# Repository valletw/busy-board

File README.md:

# Busy Board

My son wanted a busy board and I took the challenge to do my own, fully managed
by hardware (no MCU, no software).

Here is a fully hardware managed busy board with buttons & LEDs and an incremental
counter displayed on 7-segments display or LEDs track. Counter increment speed
can be switched with rotary switch from manual (button) to 4 Hz. To avoid buying
coin cells, I added a Lithium battery charger with an USB-C port: charge power
can be set with a DIP switch.

## Hardware

Power:

- USB-C Lipo battery charger (check EEMB 3.7V battery)
- Power switch to completely cut the power supply
- Polarity check
- LED are powered with 3.3V (LDO) or 5V (Boost regulator) from battery

Frequencies (improve battery consumption):

- An RC oscillator generate a 512 Hz frequency
- A binary counter generate multiple sub-frequencies from the 512 Hz
- A saw signal is generate from 128 Hz to generate LED PWM
- PWM duty cycle can be adjusted with potentiometer

Switches:

- 6 push switches that control 6 LEDs: Red, Orange, Green, White, Blue and Purple
- 3 rotary switch to control Red, Green, Blue LED power (change PWM duty cycle)
- Counter selector to switch between: 7-segments, LED track or unique LED
- Rotary switch to select counter speed: Button, 0.5 Hz, 1 Hz, 2 Hz or 4 Hz.

Note: All switches are similar but mechanical part will be 3D printed to provide
multiple type of switches: Push, Rocker, Toggle, Rotary, Key, Wire.

### Manufacturing

The board is manufactured by [JLCPCB](https://jlcpcb.com), here is the details
you will require to generate an order.

*Note: JLCPCB requests some modifications on output files, do not use direct
export from KiCad (check the FAQ)*

#### PCB

Files: [Gerbers](jlcpcb/gerbers.zip)

Configuration              | Value
---------------------------|---------------------------------
Base Materiel              | FR-4
Layers                     | 4
Dimensions                 | 140 x 180 mm
Different design           | 1
Delivery format            | Single PCB
PCB thickness              | 1.0 mm
PCB color                  | Green (other colors have fees)
Silkscreen                 | White
Materiel type              | FR4 TG135
Surface finish             | LeadFree HASL
Specify stackup            | No requirement
Via covering               | Plugged
Min via hole size/diameter | 0.3mm/0.45mm

*Note: All options have not been detail here, keep default value.*

#### Assembly

The project use 54 references with 26 extended. Extended parts bring extra cost
during assembly, around ~3$ per reference (no matter the number of components to
solder). To reduce the cost for small batch I propose two assembly configuration:

- Full: All managed by JLCPCB
- Partial: Basic parts and few extended parts are assembled per JLCPCB, and
  remaining parts can be buy on LCSC and soldered manually.

Files:

- [BOM Full](jlcpcb/bom-full.csv)
- [BOM Partial](jlcpcb/bom-partial.csv) - [BOM Extended](jlcpcb/bom-extended.csv)
- [CPL](jlcpcb/cpl.csv)

Configuration           | Value
------------------------|--------------------
PCBA type               | Economic
Assembly side           | Top
Tooling holes           | Added by JLCPCB
Confirm Parts Placement | Yes

Verify "pick & place" orientations and positions on the web viewer

*Note: All options have not been detail here, keep default value.*

## Mechanical

3D printed parts will be provided in this repository: casing, switches, light guides.

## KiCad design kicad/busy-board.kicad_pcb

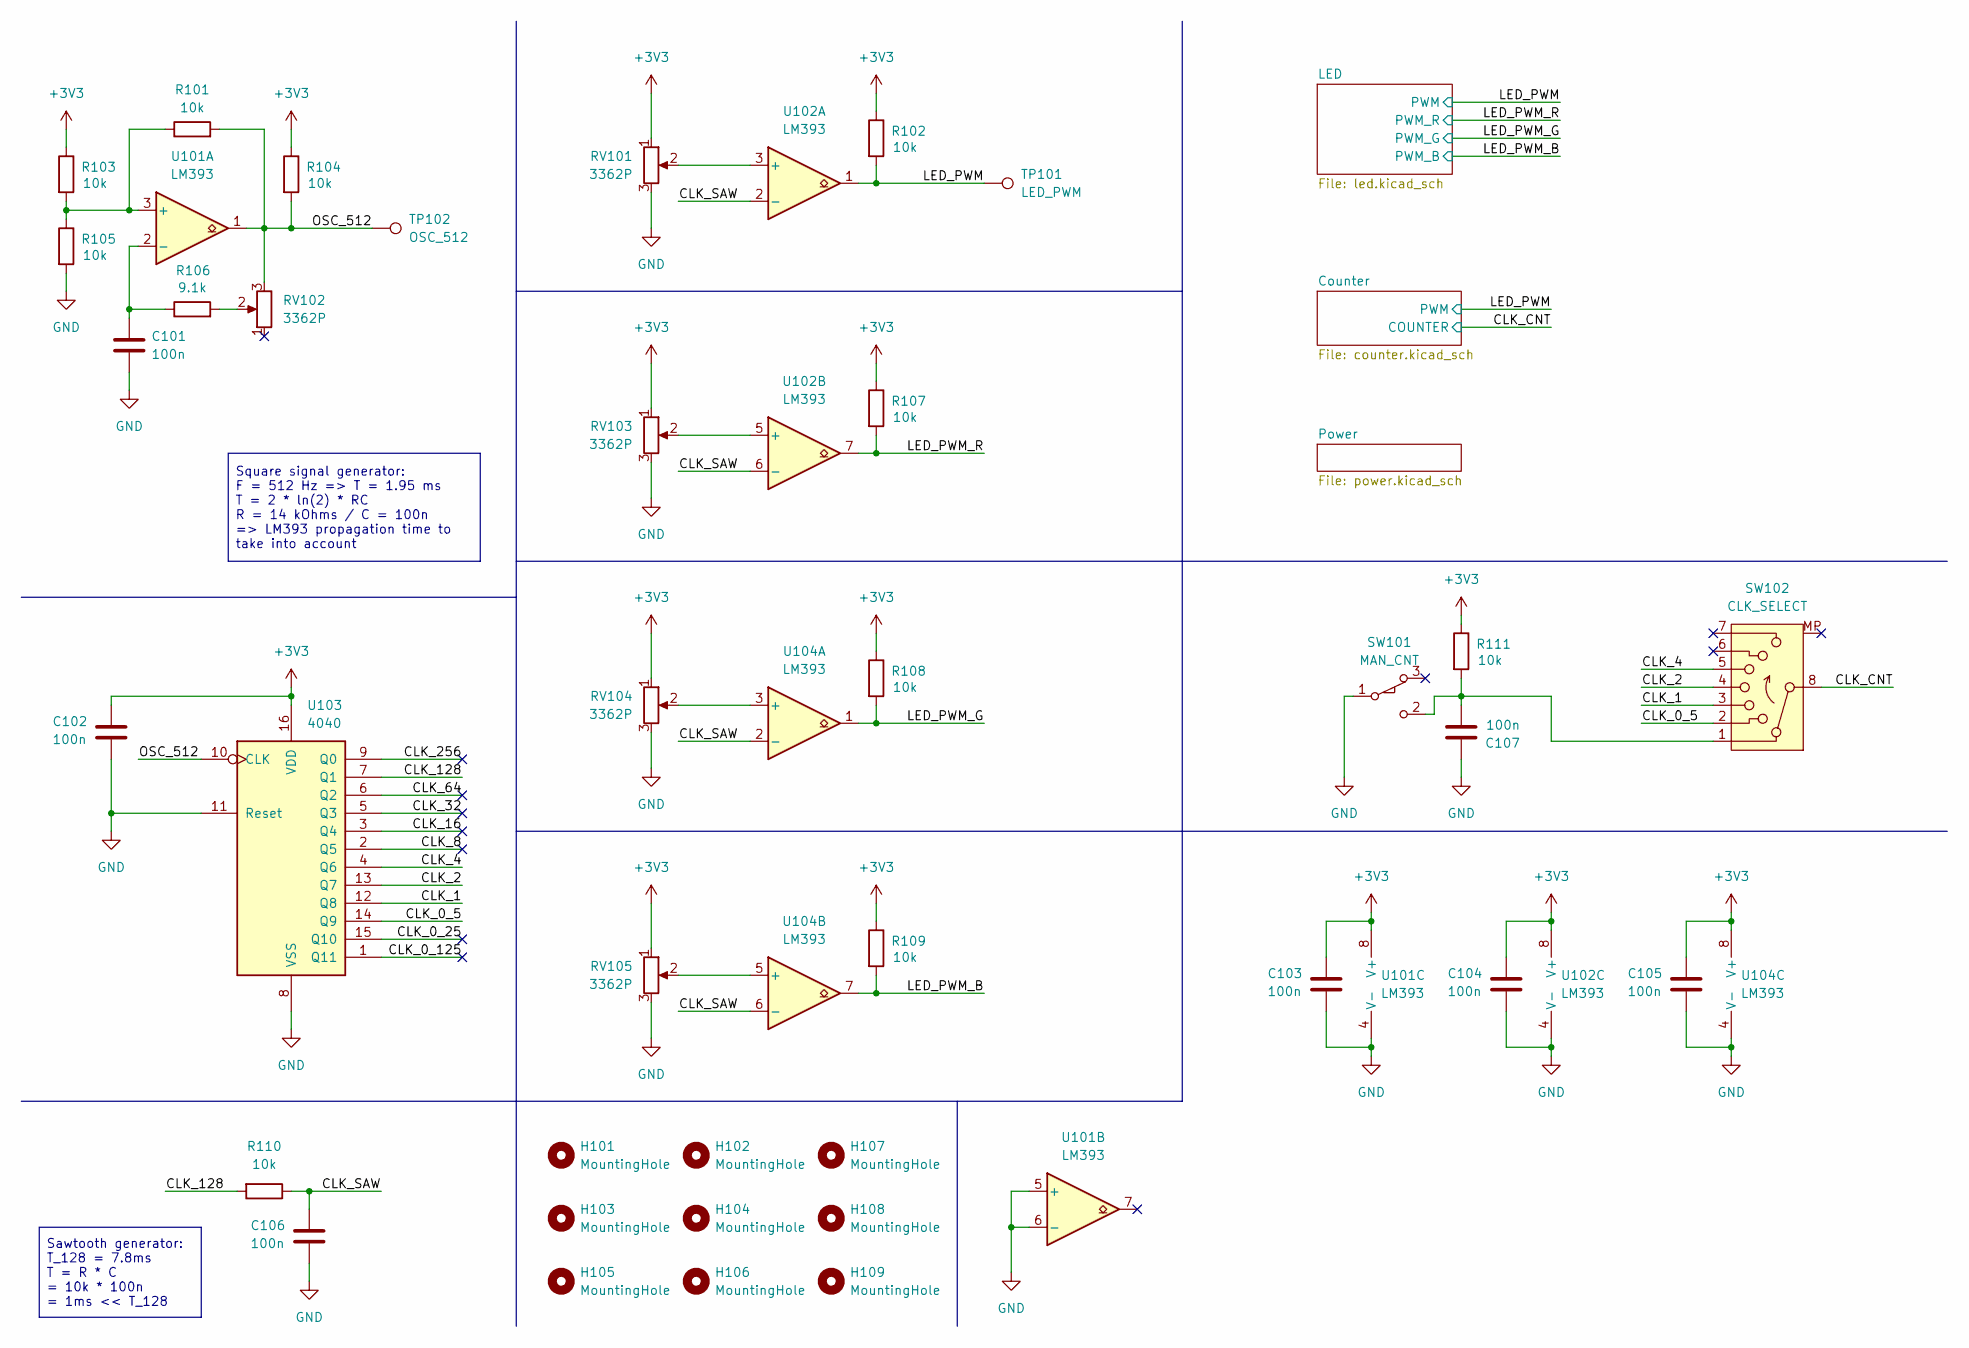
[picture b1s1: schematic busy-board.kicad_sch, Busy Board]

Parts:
C101: 100n; C_0603_1608Metric; MFR Part # CC0603JRX7R7BB104; LCSC Part # C91183
C102, C103, C104, C105, C106, C107: 100n; C_0402_1005Metric; MFR Part # CL05B104KB54PNC; LCSC Part # C307331
H101, H102, H103, H104, H105, H106, H107, H108, H109: MountingHole; MountingHole_2.7mm_M2.5_ISO7380
R101, R102, R103, R104, R105, R107, R108, R109, R110, R111: 10k; R_0603_1608Metric; MFR Part # 0603WAF1002T5E; LCSC Part # C25804
R106: 9.1k; R_0603_1608Metric; MFR Part # 0603WAF9101T5E; LCSC Part # C23260
RV101, RV102, RV103, RV104, RV105: 3362P; BOURNS_3362P; MFR Part # 3362P-1-103LF; LCSC Part # C58159
SW101: MAN_CNT; SW-TH_DM1-12UP-1; MFR Part # DM1-12UP-1; LCSC Part # C405949
SW102: CLK_SELECT; SW-TH_RT-0C4-D; MFR Part # RT-0C5; LCSC Part # C508440
TP101: LED_PWM; TestPoint_Pad_D1.5mm
TP102: OSC_512; TestPoint_Pad_D1.5mm
U101, U102, U104: LM393; SOIC-8_3.9x4.9mm_P1.27mm; MFR Part # LM393DR2G; LCSC Part # C7955
U103: 4040; SOP-16_4.4x10.4mm_P1.27mm; MFR Part # CD4040BM/TR; LCSC Part # C725347

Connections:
+3V3: C102.1, C103.1, C104.1, C105.1, R102.1, R103.1, R104.1, R107.1, R108.1, R109.1, R111.1, RV101.1, RV103.1, RV104.1, RV105.1, U101.8 (V+), U102.8 (V+), U103.16 (VDD), U104.8 (V+); also elsewhere on the board
/CLK_0_5: SW102.2, U103.14 (Q9)
/CLK_0_25: U103.15 (Q10)
/CLK_0_125: U103.1 (Q11)
/CLK_1: SW102.3, U103.12 (Q8)
/CLK_2: SW102.4, U103.13 (Q7)
/CLK_4: SW102.5, U103.4 (Q6)
/CLK_8: U103.2 (Q5)
/CLK_16: U103.3 (Q4)
/CLK_32: U103.5 (Q3)
/CLK_64: U103.6 (Q2)
/CLK_128: R110.2, U103.7 (Q1)
/CLK_256: U103.9 (Q0)
/CLK_CNT: SW102.8; also elsewhere on the board
/CLK_SAW: C106.1, R110.1, U102.2 (-), U102.6 (-), U104.2 (-), U104.6 (-)
/LED_PWM: R102.2, TP101.1, U102.1; also elsewhere on the board
/LED_PWM_B: R109.2, U104.7; also elsewhere on the board
/LED_PWM_G: R108.2, U104.1; also elsewhere on the board
/LED_PWM_R: R107.2, U102.7; also elsewhere on the board
/OSC_512: R101.2, R104.2, RV102.3, TP102.1, U101.1, U103.10 (CLK)
GND: C101.2, C102.2, C103.2, C104.2, C105.2, C106.2, C107.1, R105.2, RV101.3, RV103.3, RV104.3, RV105.3, SW101.1 (A), U101.4 (V-), U101.5 (+), U101.6 (-), U102.4 (V-), U103.8 (VSS), U103.11 (Reset), U104.4 (V-); also elsewhere on the board
unnamed: R106.2, RV102.2
unnamed: C107.2, R111.2, SW101.2 (B), SW102.1
unnamed: R101.1, R103.2, R105.1, U101.3 (+)
unnamed: C101.1, R106.1, U101.2 (-)
unnamed: RV101.2, U102.3 (+)
unnamed: RV103.2, U102.5 (+)
unnamed: RV104.2, U104.3 (+)
unnamed: RV105.2, U104.5 (+)

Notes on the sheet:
Sawtooth generator: T_128 = 7.8ms T = R * C = 10k * 100n = 1ms << T_128
Square signal generator: F = 512 Hz => T = 1.95 ms T = 2 * ln(2) * RC R = 14 kOhms / C = 100n => LM393 propagation time to take into account

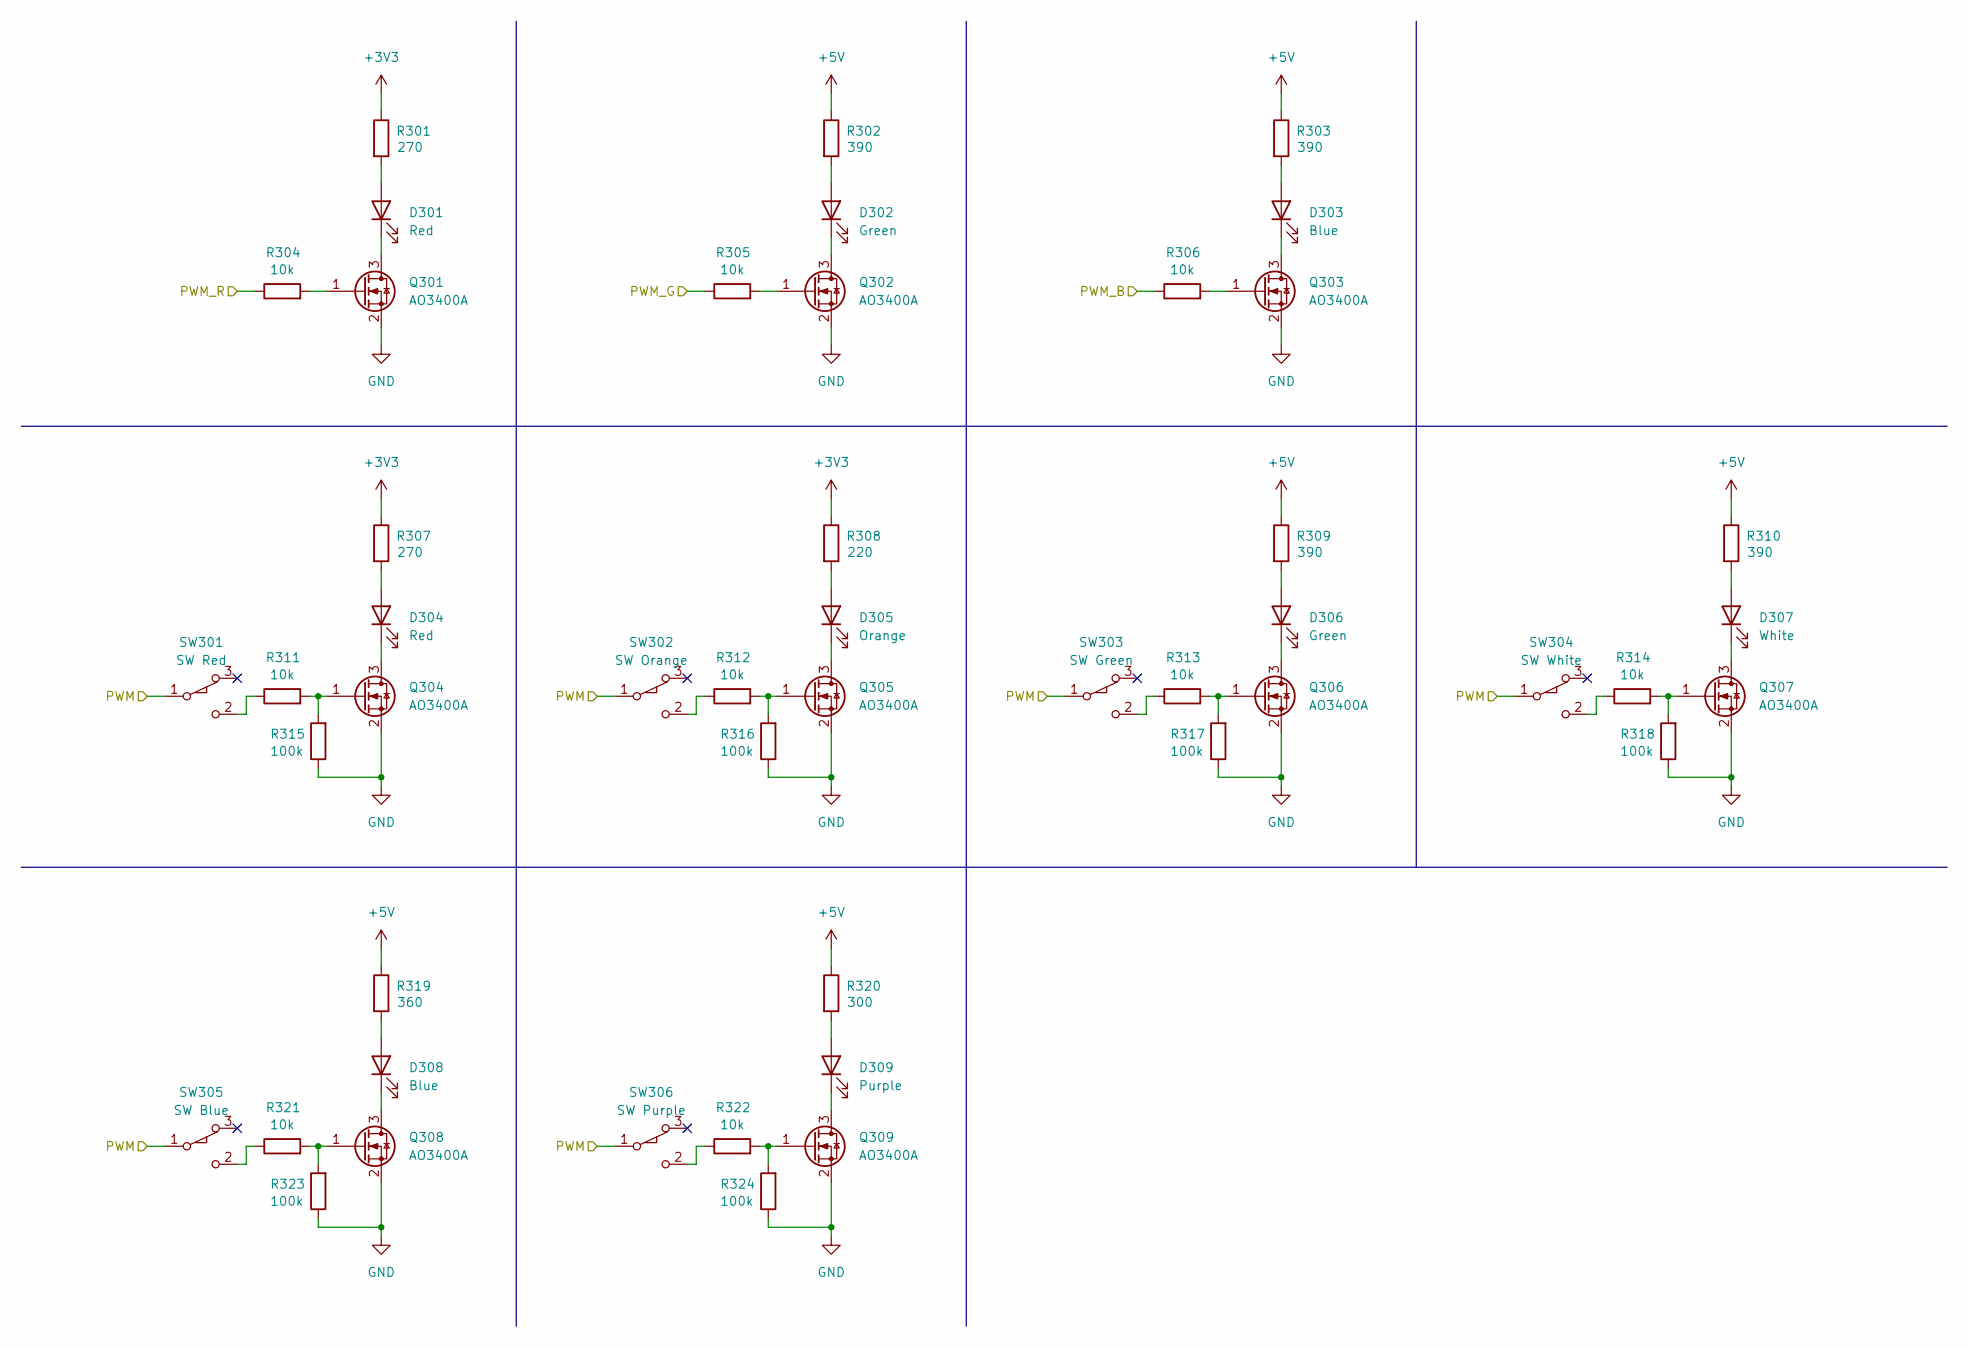
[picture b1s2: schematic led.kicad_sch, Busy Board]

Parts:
D301, D304: Red; LED_0805_2012Metric; MFR Part # NCD0805R1; LCSC Part # C84256
D302, D306: Green; LED_0805_2012Metric; MFR Part # KT-0805G; LCSC Part # C2297
D303, D308: Blue; LED_0805_2012Metric; MFR Part # NCD0805B2; LCSC Part # C84259
D305: Orange; LED_0805_2012Metric; MFR Part # NCD0805O1; LCSC Part # C84262
D307: White; LED_0805_2012Metric; MFR Part # KT-0805W; LCSC Part # C34499
D309: Purple; LED_0805_2012Metric; MFR Part # XL-2012UVA; LCSC Part # C7371915
Q301, Q302, Q303, Q304, Q305, Q306, Q307, Q308, Q309: AO3400A; SOT-23; MFR Part # AO3400A; LCSC Part # C20917
R301, R307: 270; R_0603_1608Metric; MFR Part # 0603WAF2700T5E; LCSC Part # C22966
R302, R303, R309, R310: 390; R_0603_1608Metric; MFR Part # 0603WAF3900T5E; LCSC Part # C23151
R304, R305, R306, R311, R312, R313, R314, R321, R322: 10k; R_0603_1608Metric; MFR Part # 0603WAF1002T5E; LCSC Part # C25804
R308: 220; R_0603_1608Metric; MFR Part # 0603WAF2200T5E; LCSC Part # C22962
R315, R316, R317, R318, R323, R324: 100k; R_0603_1608Metric; MFR Part # 0603WAF1003T5E; LCSC Part # C25803
R319: 360; R_0603_1608Metric; MFR Part # 0603WAF3600T5E; LCSC Part # C25194
R320: 300; R_0603_1608Metric; MFR Part # 0603WAF3000T5E; LCSC Part # C23025
SW301: SW Red; SW-TH_DM1-12UP-1; MFR Part # DM1-12UP-1; LCSC Part # C405949
SW302: SW Orange; SW-TH_DM1-12UP-1; MFR Part # DM1-12UP-1; LCSC Part # C405949
SW303: SW Green; SW-TH_DM1-12UP-1; MFR Part # DM1-12UP-1; LCSC Part # C405949
SW304: SW White; SW-TH_DM1-12UP-1; MFR Part # DM1-12UP-1; LCSC Part # C405949
SW305: SW Blue; SW-TH_DM1-12UP-1; MFR Part # DM1-12UP-1; LCSC Part # C405949
SW306: SW Purple; SW-TH_DM1-12UP-1; MFR Part # DM1-12UP-1; LCSC Part # C405949

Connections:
+3V3: R301.1, R307.1, R308.1; also elsewhere on the board
+5V: R302.1, R303.1, R309.1, R310.1, R319.1, R320.1; also elsewhere on the board
/LED_PWM: SW301.1 (A), SW302.1 (A), SW303.1 (A), SW304.1 (A), SW305.1 (A), SW306.1 (A); also elsewhere on the board
/LED_PWM_B: R306.1; also elsewhere on the board
/LED_PWM_G: R305.1; also elsewhere on the board
/LED_PWM_R: R304.1; also elsewhere on the board
GND: Q301.2 (S), Q302.2 (S), Q303.2 (S), Q304.2 (S), Q305.2 (S), Q306.2 (S), Q307.2 (S), Q308.2 (S), Q309.2 (S), R315.1, R316.1, R317.1, R318.1, R323.1, R324.1; also elsewhere on the board
unnamed: D301.2 (A), R301.2
unnamed: D301.1 (K), Q301.3 (D)
unnamed: D302.2 (A), R302.2
unnamed: D302.1 (K), Q302.3 (D)
unnamed: D303.2 (A), R303.2
unnamed: D303.1 (K), Q303.3 (D)
unnamed: D304.2 (A), R307.2
unnamed: D304.1 (K), Q304.3 (D)
unnamed: D305.2 (A), R308.2
unnamed: D305.1 (K), Q305.3 (D)
unnamed: D306.2 (A), R309.2
unnamed: D306.1 (K), Q306.3 (D)
unnamed: D307.2 (A), R310.2
unnamed: D307.1 (K), Q307.3 (D)
unnamed: D308.2 (A), R319.2
unnamed: D308.1 (K), Q308.3 (D)
unnamed: D309.2 (A), R320.2
unnamed: D309.1 (K), Q309.3 (D)
unnamed: Q301.1 (G), R304.2
unnamed: Q302.1 (G), R305.2
unnamed: Q303.1 (G), R306.2
unnamed: Q304.1 (G), R311.2, R315.2
unnamed: Q305.1 (G), R312.2, R316.2
unnamed: Q306.1 (G), R313.2, R317.2
unnamed: Q307.1 (G), R314.2, R318.2
unnamed: Q308.1 (G), R321.2, R323.2
unnamed: Q309.1 (G), R322.2, R324.2
unnamed: R311.1, SW301.2 (B)
unnamed: R312.1, SW302.2 (B)
unnamed: R313.1, SW303.2 (B)
unnamed: R314.1, SW304.2 (B)
unnamed: R321.1, SW305.2 (B)
unnamed: R322.1, SW306.2 (B)

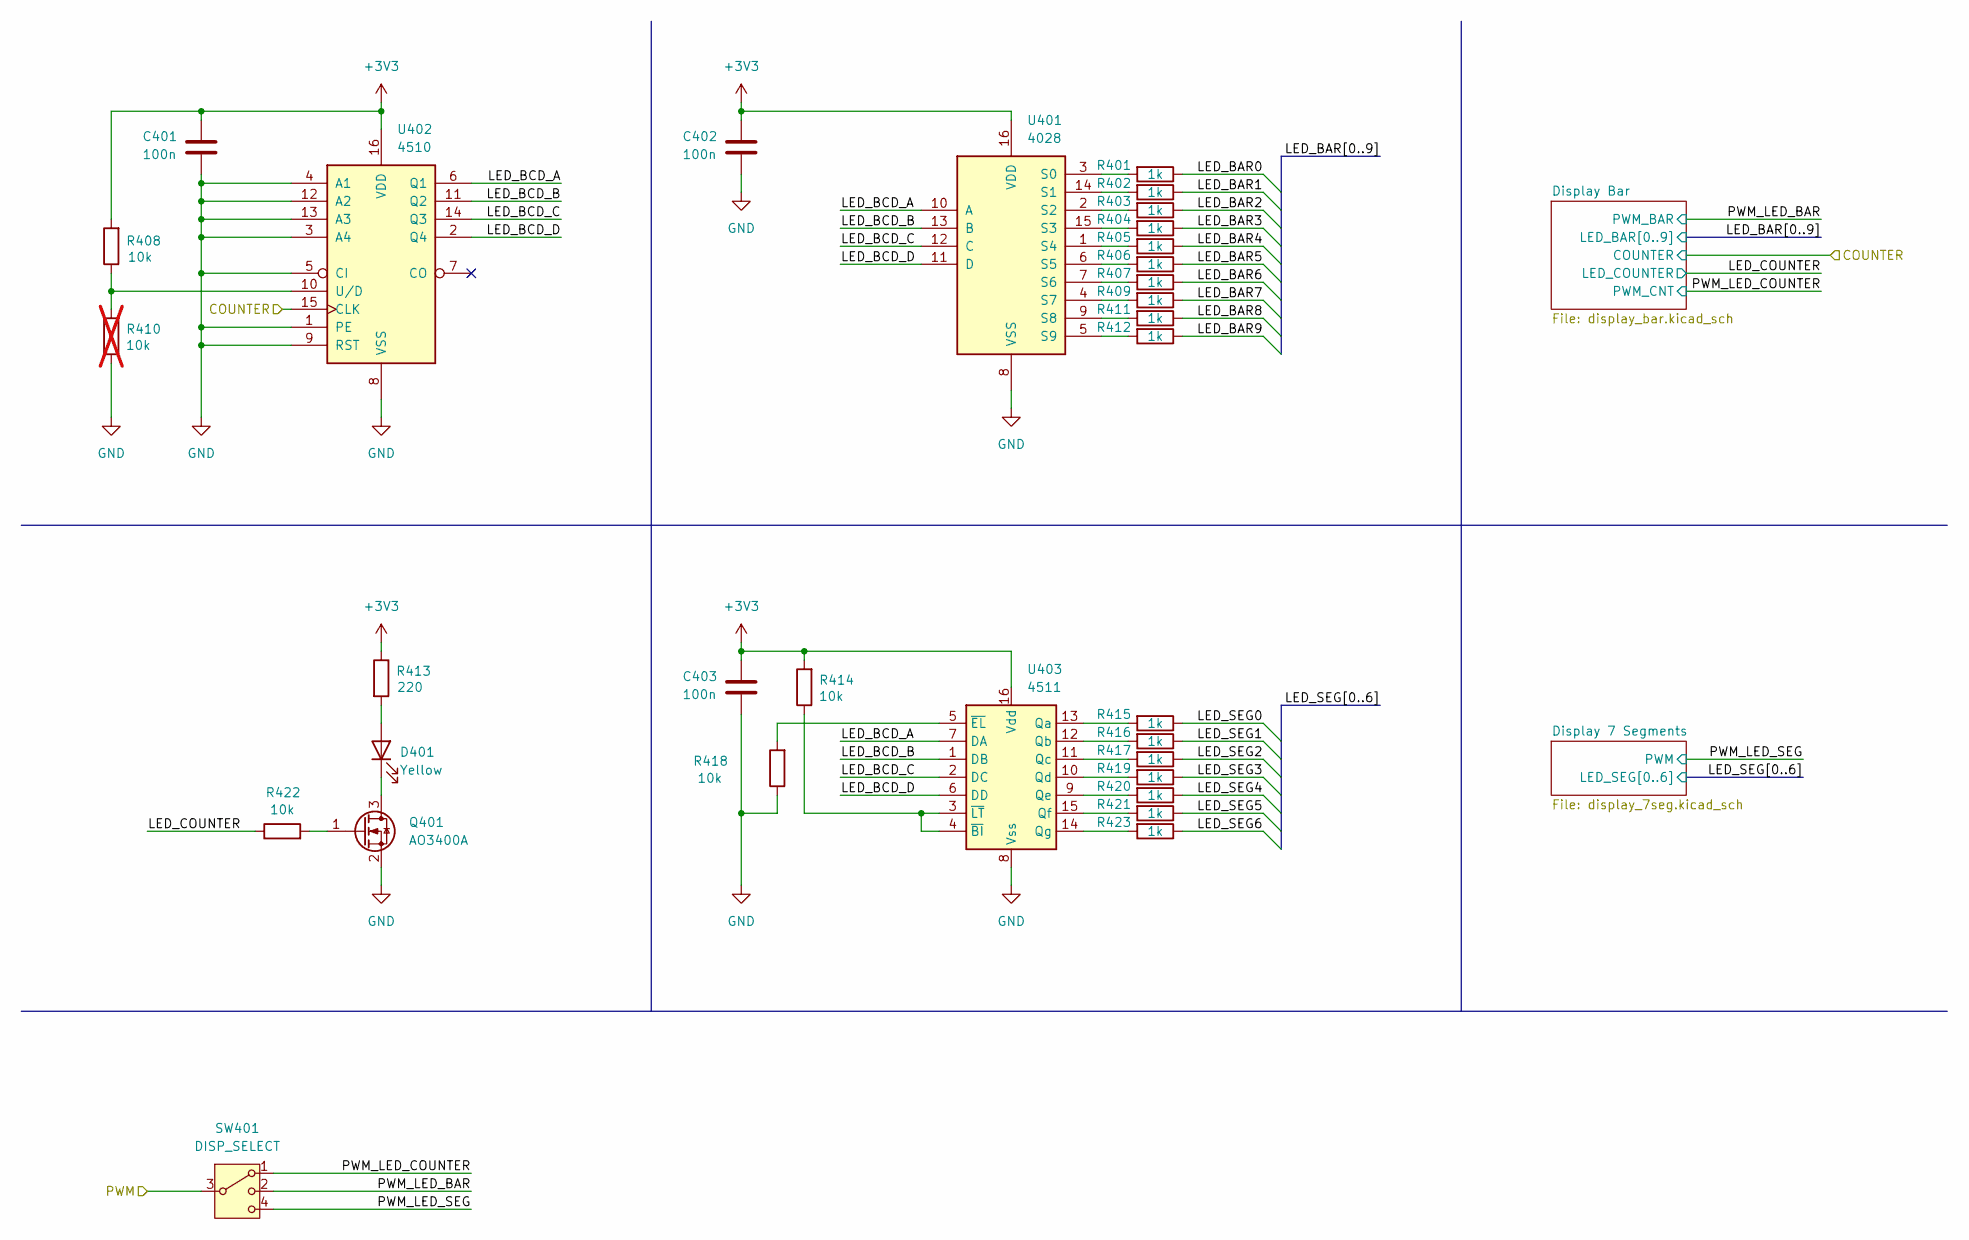
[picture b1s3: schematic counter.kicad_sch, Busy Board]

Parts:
C401, C402, C403: 100n; C_0402_1005Metric; MFR Part # CL05B104KB54PNC; LCSC Part # C307331
D401: Yellow; LED_0805_2012Metric; MFR Part # KT-0805Y; LCSC Part # C2296
Q401: AO3400A; SOT-23; MFR Part # AO3400A; LCSC Part # C20917
R401, R402, R403, R404, R405, R406, R407, R409, R411, R412, R415, R416, R417, R419, R420, R421, R423: 1k; R_0603_1608Metric; MFR Part # 0603WAF1001T5E; LCSC Part # C21190
R408, R414, R418, R422: 10k; R_0603_1608Metric; MFR Part # 0603WAF1002T5E; LCSC Part # C25804
R410: 10k; R_0603_1608Metric; MFR Part # 0603WAF1002T5E; LCSC Part # C25804; not fitted
R413: 220; R_0603_1608Metric; MFR Part # 0603WAF2200T5E; LCSC Part # C22962
SW401: DISP_SELECT; SW-TH_SS-23D06-L5; MFR Part # SS23D06L5; LCSC Part # C609829
U401: 4028; TSSOP-16_4.4x5mm_P0.65mm; MFR Part # CD4028BPWR; LCSC Part # C2653282
U402: 4510; TSSOP-16_4.4x5mm_P0.65mm; MFR Part # CD4510BPWR; LCSC Part # C2862976
U403: 4511; TSSOP-16_4.4x5mm_P0.65mm; MFR Part # CD4511BPWR; LCSC Part # C353987

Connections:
+3V3: C401.1, C402.1, C403.1, R408.2, R413.1, R414.2, U401.16 (VDD), U402.16 (VDD), U403.16 (Vdd); also elsewhere on the board
/CLK_CNT: U402.15 (CLK); also elsewhere on the board
/Counter/LED_BAR0: R401.1; also elsewhere on the board
/Counter/LED_BAR1: R402.1; also elsewhere on the board
/Counter/LED_BAR2: R403.1; also elsewhere on the board
/Counter/LED_BAR3: R404.1; also elsewhere on the board
/Counter/LED_BAR4: R405.1; also elsewhere on the board
/Counter/LED_BAR5: R406.1; also elsewhere on the board
/Counter/LED_BAR6: R407.1; also elsewhere on the board
/Counter/LED_BAR7: R409.1; also elsewhere on the board
/Counter/LED_BAR8: R411.1; also elsewhere on the board
/Counter/LED_BAR9: R412.1; also elsewhere on the board
/Counter/LED_BCD_A: U401.10 (A), U402.6 (Q1), U403.7 (DA)
/Counter/LED_BCD_B: U401.13 (B), U402.11 (Q2), U403.1 (DB)
/Counter/LED_BCD_C: U401.12 (C), U402.14 (Q3), U403.2 (DC)
/Counter/LED_BCD_D: U401.11 (D), U402.2 (Q4), U403.6 (DD)
/Counter/LED_COUNTER: R422.1; also elsewhere on the board
/Counter/LED_SEG0: R415.1; also elsewhere on the board
/Counter/LED_SEG1: R416.1; also elsewhere on the board
/Counter/LED_SEG2: R417.1; also elsewhere on the board
/Counter/LED_SEG3: R419.1; also elsewhere on the board
/Counter/LED_SEG4: R420.1; also elsewhere on the board
/Counter/LED_SEG5: R421.1; also elsewhere on the board
/Counter/LED_SEG6: R423.1; also elsewhere on the board
/Counter/PWM_LED_BAR: SW401.2; also elsewhere on the board
/Counter/PWM_LED_COUNTER: SW401.1; also elsewhere on the board
/Counter/PWM_LED_SEG: SW401.4; also elsewhere on the board
/LED_PWM: SW401.3; also elsewhere on the board
GND: C401.2, C402.2, C403.2, Q401.2 (S), R410.1, R418.1, U401.8 (VSS), U402.1 (PE), U402.3 (A4), U402.4 (A1), U402.5 (CI), U402.8 (VSS), U402.9 (RST), U402.12 (A2), U402.13 (A3), U403.8 (Vss); also elsewhere on the board
unnamed: D401.2 (A), R413.2
unnamed: D401.1 (K), Q401.3 (D)
unnamed: Q401.1 (G), R422.2
unnamed: R401.2, U401.3 (S0)
unnamed: R402.2, U401.14 (S1)
unnamed: R403.2, U401.2 (S2)
unnamed: R404.2, U401.15 (S3)
unnamed: R405.2, U401.1 (S4)
unnamed: R406.2, U401.6 (S5)
unnamed: R407.2, U401.7 (S6)
unnamed: R409.2, U401.4 (S7)
unnamed: R411.2, U401.9 (S8)
unnamed: R412.2, U401.5 (S9)
unnamed: R408.1, R410.2, U402.10 (U/D)
unnamed: R415.2, U403.13 (Qa)
unnamed: R416.2, U403.12 (Qb)
unnamed: R417.2, U403.11 (Qc)
unnamed: R419.2, U403.10 (Qd)
unnamed: R420.2, U403.9 (Qe)
unnamed: R421.2, U403.15 (Qf)
unnamed: R423.2, U403.14 (Qg)
unnamed: R414.1, U403.3 (~LT), U403.4 (~BI)
unnamed: R418.2, U403.5 (~EL)

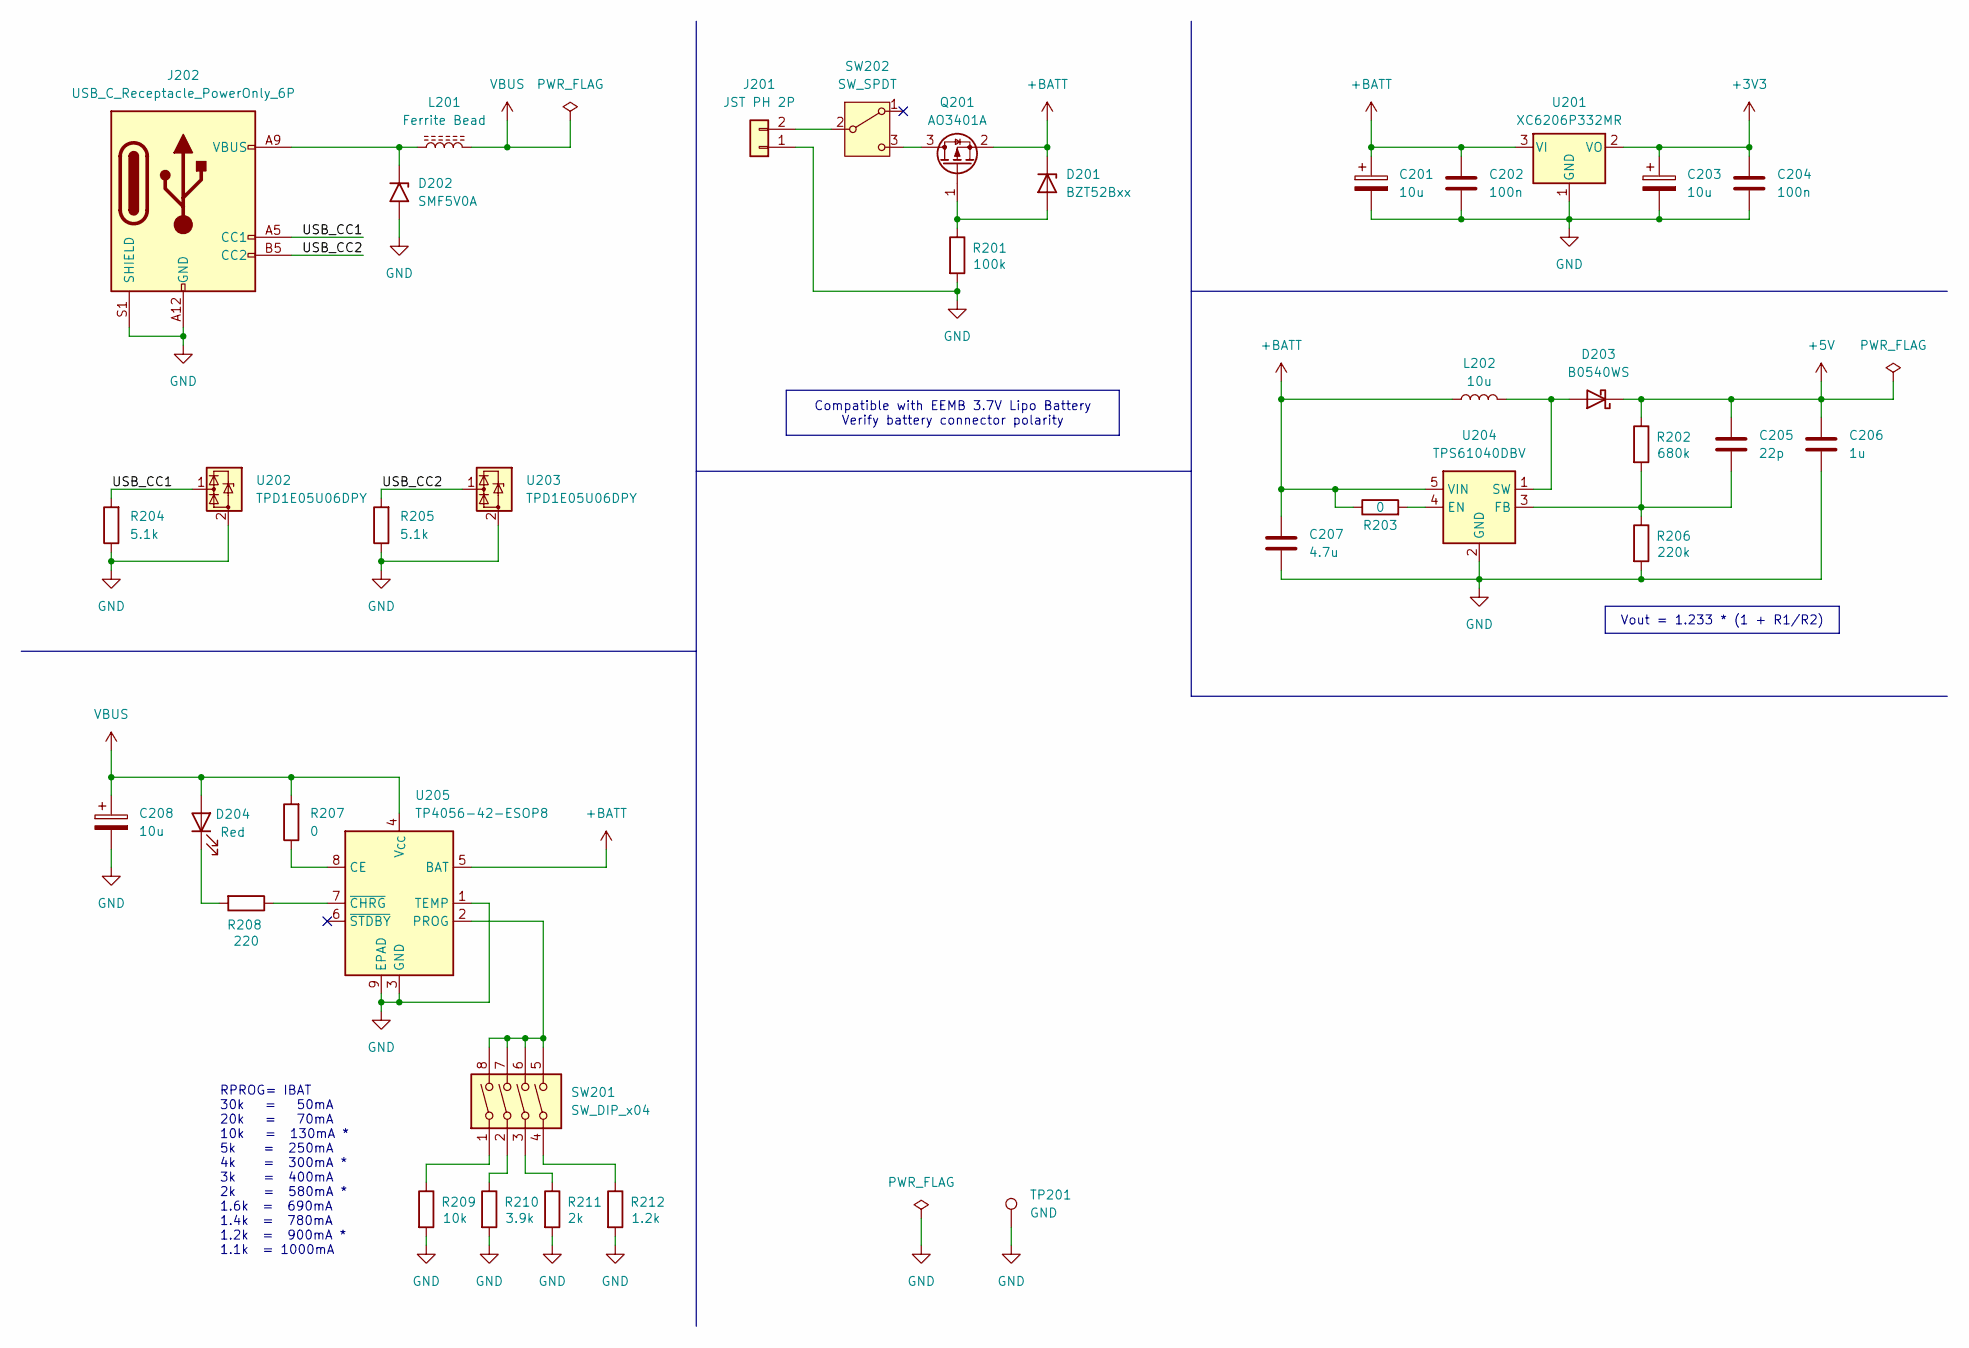
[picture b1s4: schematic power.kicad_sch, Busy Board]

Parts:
C201, C203, C208: 10u; CP_EIA-3216-18_Kemet-A; MFR Part # TAJA106K016RNJ; LCSC Part # C7171
C202, C204: 100n; C_0603_1608Metric; MFR Part # CC0603KRX7R9BB104; LCSC Part # C14663
C205: 22p; C_0603_1608Metric; MFR Part # CL10C220JB8NNNC; LCSC Part # C1653
C206: 1u; C_0603_1608Metric; MFR Part # CL10A105KB8NNNC; LCSC Part # C15849
C207: 4.7u; C_0603_1608Metric; MFR Part # CL10A475KO8NNNC; LCSC Part # C19666
D201: BZT52Bxx; D_SOD-123F; MFR Part # BZT52B5V1; LCSC Part # C19077393
D202: SMF5V0A; D_SMF; MFR Part # SMF5.0A; LCSC Part # C19077497
D203: B0540WS; D_SOD-323; MFR Part # B0540WS; LCSC Part # C7420326
D204: Red; LED_0805_2012Metric; MFR Part # NCD0805R1; LCSC Part # C84256
J201: JST PH 2P; JST_PH_S2B-PH-K_1x02_P2.00mm_Horizontal; MFR Part # S2B-PH-K-S(LF)(SN); LCSC Part # C173752
J202: USB_C_Receptacle_PowerOnly_6P; USB_C_Receptacle_HRO_TYPE-C-31-M-17; MFR Part # TYPE-C-31-M-17; LCSC Part # C283540
L201: Ferrite Bead; L_0603_1608Metric; MFR Part # BLM18PG121SN1D; LCSC Part # C14709
L202: 10u; L_0603_1608Metric; MFR Part # SDFL1608S100KTF; LCSC Part # C1035
Q201: AO3401A; SOT-23; MFR Part # AO3401A; LCSC Part # C15127
R201: 100k; R_0603_1608Metric; MFR Part # 0603WAF1003T5E; LCSC Part # C25803
R202: 680k; R_0603_1608Metric; MFR Part # 0603WAF6803T5E; LCSC Part # C25822
R203, R207: 0; R_0603_1608Metric; MFR Part # 0603WAF0000T5E; LCSC Part # C21189
R204, R205: 5.1k; R_0402_1005Metric; MFR Part # 0402WGF5101TCE; LCSC Part # C25905
R206: 220k; R_0603_1608Metric; MFR Part # 0603WAF2203T5E; LCSC Part # C22961
R208: 220; R_0402_1005Metric; MFR Part # 0402WGF5101TCE; LCSC Part # C25905
R209: 10k; R_0603_1608Metric; MFR Part # 0603WAF1002T5E; LCSC Part # C25804
R210: 3.9k; R_0603_1608Metric; MFR Part # 0603WAF3901T5E; LCSC Part # C23018
R211: 2k; R_0603_1608Metric; MFR Part # 0603WAF2001T5E; LCSC Part # C22975
R212: 1.2k; R_0603_1608Metric; MFR Part # 0603WAF1201T5E; LCSC Part # C22765
SW201: SW_DIP_x04; SW_DIP_SPSTx04_Slide_9.78x12.34mm_W7.62mm_P2.54mm; MFR Part # DSWB04LHGET; LCSC Part # C99418
SW202: SW_SPDT; SW_SPDT_Shouhan_MSK12C02; MFR Part # MSK12C02; LCSC Part # C431540
TP201: GND; TestPoint_Pad_4.0x4.0mm
U201: XC6206P332MR; SOT-23-3; MFR Part # XC6206P332MR-G; LCSC Part # C5446
U202, U203: TPD1E05U06DPY; Texas_DPY0002A_0.6x1mm_P0.65mm; MFR Part # TPD1E05U06DPYT; LCSC Part # C1847651
U204: TPS61040DBV; SOT-23-5; MFR Part # TPS61040DBVR; LCSC Part # C7722
U205: TP4056-42-ESOP8; MFR Part # TP4056-42-ESOP8; LCSC Part # C16581

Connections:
+3V3: C203.1, C204.1, U201.2 (VO); also elsewhere on the board
+5V: C205.1, C206.1, D203.1 (K), R202.1; also elsewhere on the board
+BATT: C201.1, C202.1, C207.1, D201.1 (K), L202.1, Q201.2 (S), R203.1, U201.3 (VI), U204.5 (VIN), U205.5 (BAT)
/Power/USB_CC1: J202.A5 (CC1), R204.2, U202.1 (I/O)
/Power/USB_CC2: J202.B5 (CC2), R205.2, U203.1 (I/O)
GND: C201.2, C202.2, C203.2, C204.2, C206.2, C207.2, C208.2, D202.2 (A2), J201.1, J202.A12 (GND), J202.B12 (GND), J202.S1 (SHIELD), R201.2, R204.1, R205.1, R206.2, R209.2, R210.2, R211.2, R212.2, TP201.1, U201.1 (GND), U202.2 (GND), U203.2 (GND), U204.2 (GND), U205.1 (TEMP), U205.3 (GND), U205.9 (EPAD); also elsewhere on the board
unnamed: D201.2 (A), Q201.1 (G), R201.1
unnamed: D202.1 (A1), J202.A9 (VBUS), J202.B9 (VBUS), L201.1
unnamed: D203.2 (A), L202.2, U204.1 (SW)
unnamed: D204.1 (K), R208.2
unnamed: J201.2, SW202.2 (B)
unnamed: Q201.3 (D), SW202.3 (C)
unnamed: R209.1, SW201.1
unnamed: R210.1, SW201.2
unnamed: R211.1, SW201.3
unnamed: R212.1, SW201.4
unnamed: R203.2, U204.4 (EN)
unnamed: C205.2, R202.2, R206.1, U204.3 (FB)
unnamed: R207.1, U205.8 (CE)
unnamed: SW201.5, SW201.6, SW201.7, SW201.8, U205.2 (PROG)
unnamed: R208.1, U205.7 (~CHRG)
VBUS: C208.1, D204.2 (A), L201.2, R207.2, U205.4 (V_{CC})

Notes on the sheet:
RPROG= IBAT 30k = 50mA 20k = 70mA 10k = 130mA * 5k = 250mA 4k = 300mA * 3k = 400mA 2k = 580mA * 1.6k = 690mA 1.4k = 780mA 1.2k = 900mA * 1.1k = 1000mA
Compatible with EEMB 3.7V Lipo Battery Verify battery connector polarity
Vout = 1.233 * (1 + R1/R2)

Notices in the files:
kicad/busy-board.kicad_pcb:
MIT License
